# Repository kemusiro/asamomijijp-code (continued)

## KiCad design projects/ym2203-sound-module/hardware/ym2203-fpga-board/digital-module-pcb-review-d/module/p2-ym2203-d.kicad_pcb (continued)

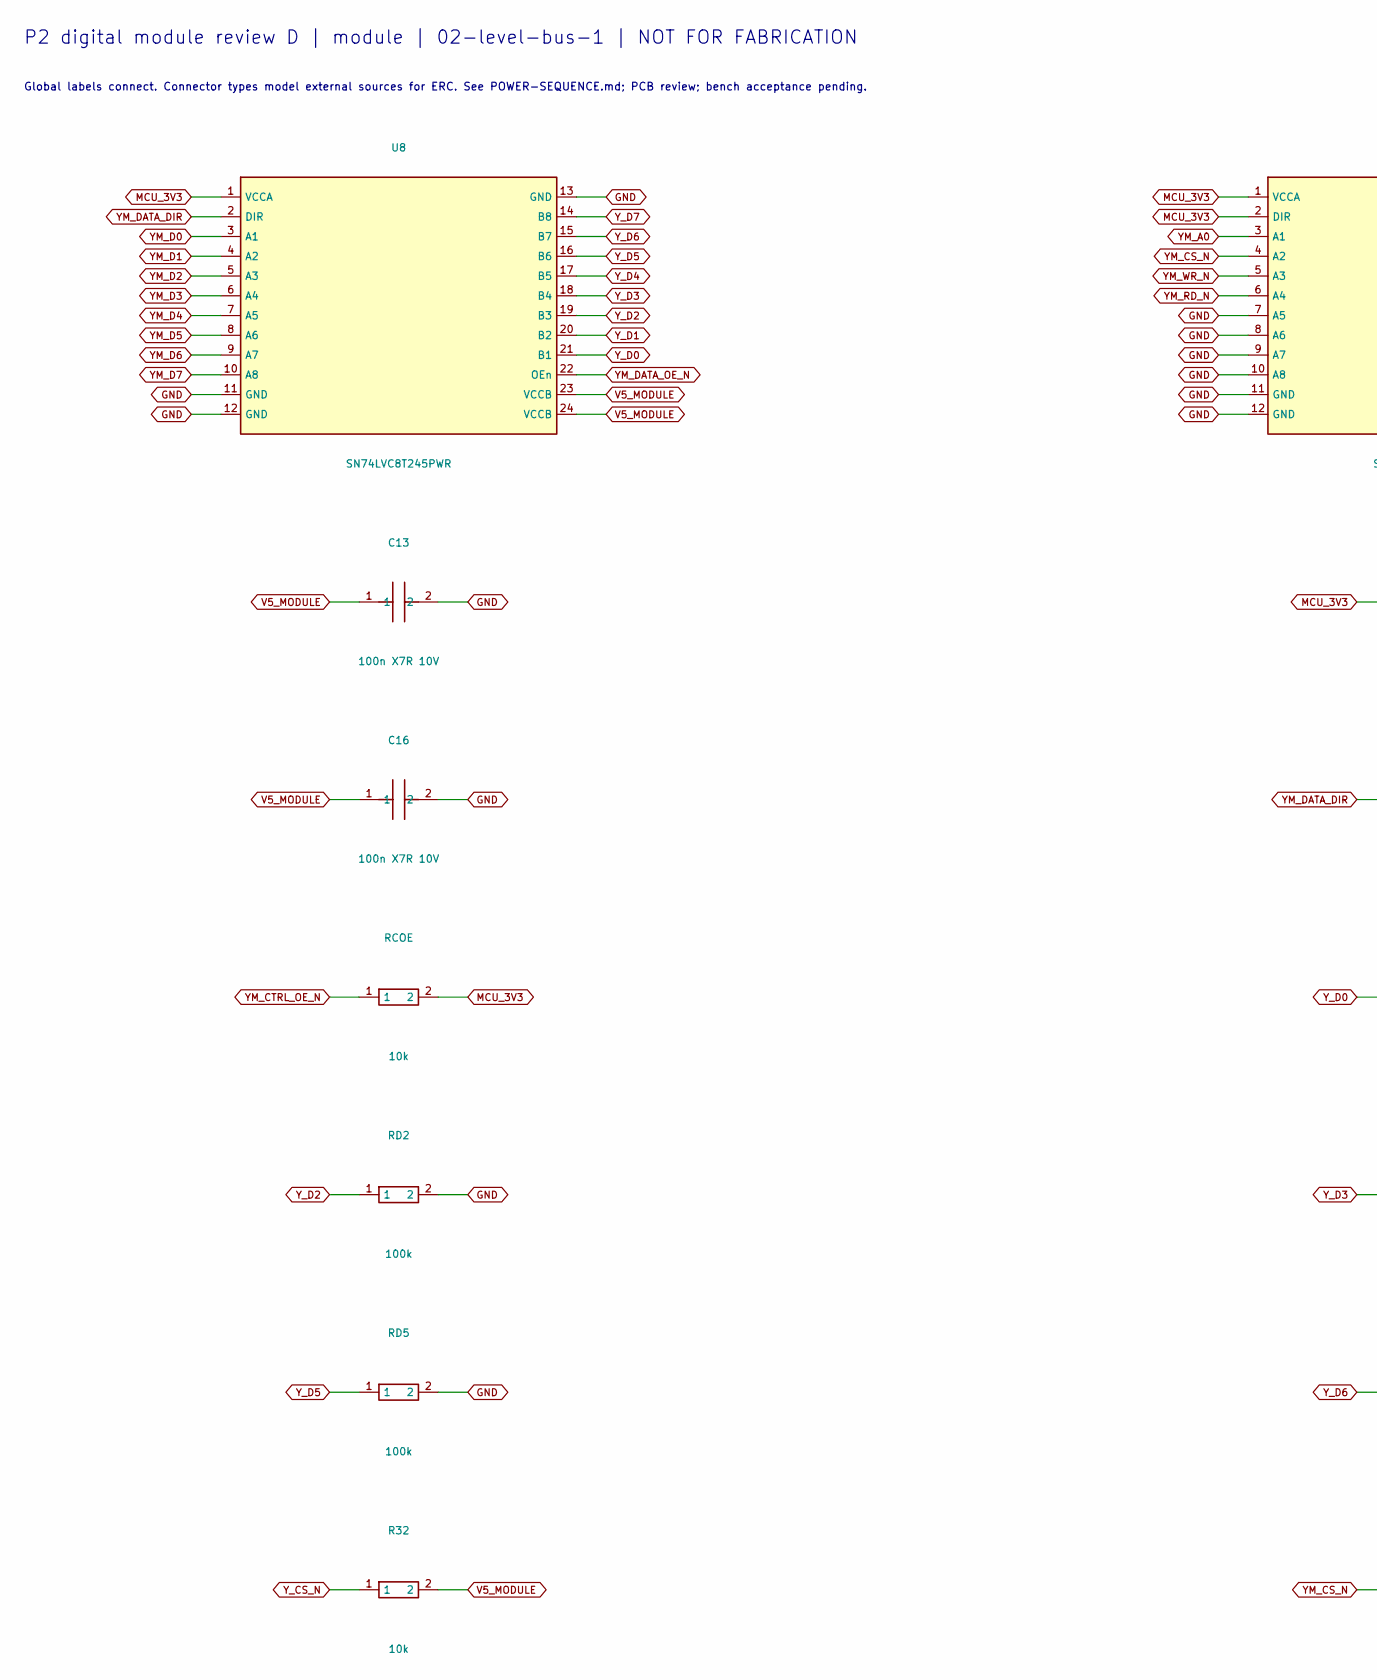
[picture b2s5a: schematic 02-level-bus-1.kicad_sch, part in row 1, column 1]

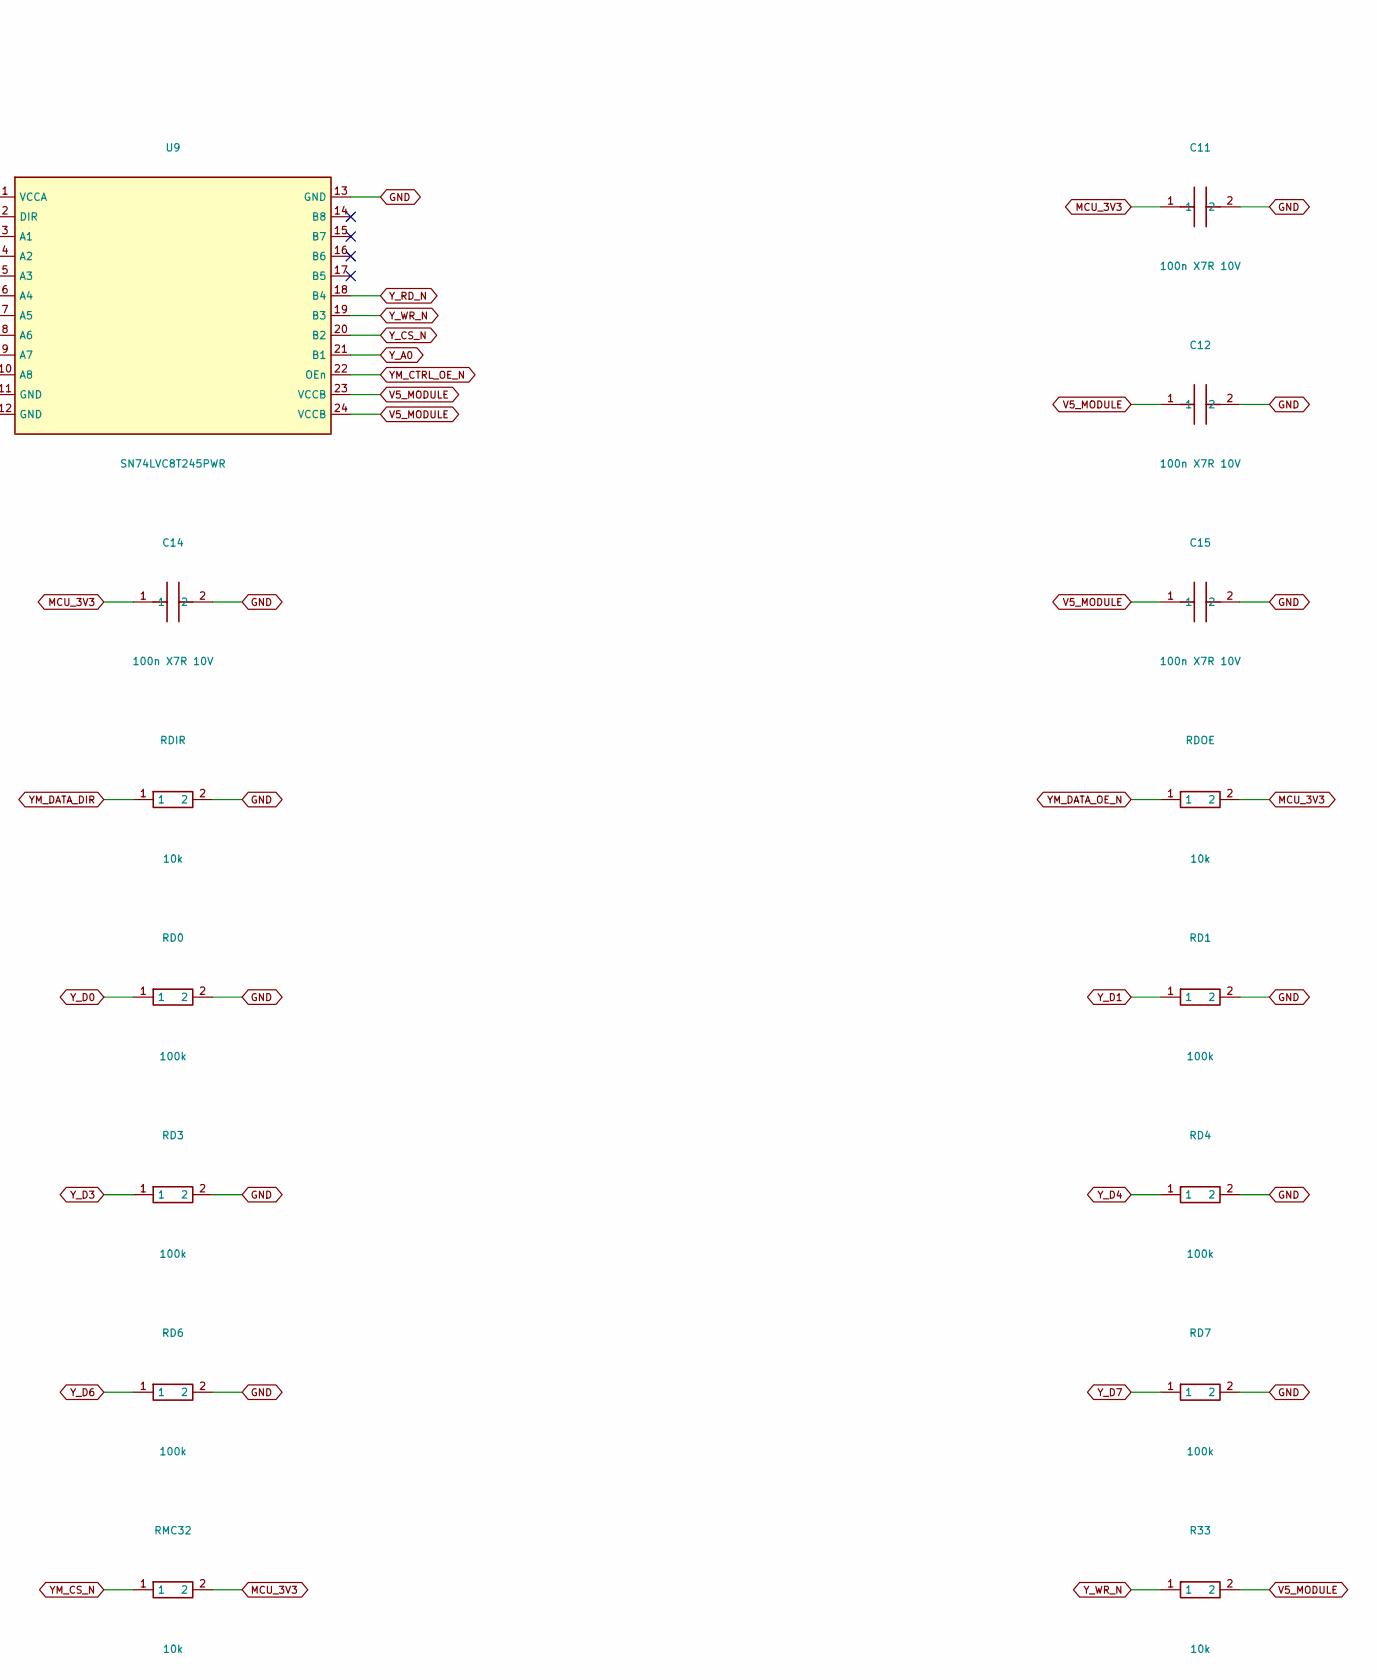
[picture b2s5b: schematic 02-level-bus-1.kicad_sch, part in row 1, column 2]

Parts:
C11, C12, C13, C14, C15, C16: 100n X7R 10V; C_0805_2012Metric
R32, R33: 10k; R_0805_2012Metric
RCOE: 10k; R_0805_2012Metric
RD0, RD1, RD2, RD3, RD4, RD5, RD6, RD7: 100k; R_0805_2012Metric
RDIR: 10k; R_0805_2012Metric
RDOE: 10k; R_0805_2012Metric
RMC32: 10k; R_0805_2012Metric
U8, U9: SN74LVC8T245PWR; TSSOP-24_4.4x7.8mm_P0.65mm

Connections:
GND: C11.2, C12.2, C13.2, C14.2, C15.2, C16.2, RD0.2, RD1.2, RD2.2, RD3.2, RD4.2, RD5.2, RD6.2, RD7.2, RDIR.2, U8.11 (GND), U8.12 (GND), U8.13 (GND), U9.7 (A5), U9.8 (A6), U9.9 (A7), U9.10 (A8), U9.11 (GND), U9.12 (GND), U9.13 (GND); also elsewhere on the board
MCU_3V3: C11.1, C14.1, RCOE.2, RDOE.2, RMC32.2, U8.1 (VCCA), U9.1 (VCCA), U9.2 (DIR); also elsewhere on the board
V5_MODULE: C12.1, C13.1, C15.1, C16.1, R32.2, R33.2, U8.23 (VCCB), U8.24 (VCCB), U9.23 (VCCB), U9.24 (VCCB); also elsewhere on the board
YM_A0: U9.3 (A1); also elsewhere on the board
YM_CS_N: RMC32.1, U9.4 (A2); also elsewhere on the board
YM_CTRL_OE_N: RCOE.1, U9.22 (OEn); also elsewhere on the board
YM_D0: U8.3 (A1); also elsewhere on the board
YM_D1: U8.4 (A2); also elsewhere on the board
YM_D2: U8.5 (A3); also elsewhere on the board
YM_D3: U8.6 (A4); also elsewhere on the board
YM_D4: U8.7 (A5); also elsewhere on the board
YM_D5: U8.8 (A6); also elsewhere on the board
YM_D6: U8.9 (A7); also elsewhere on the board
YM_D7: U8.10 (A8); also elsewhere on the board
YM_DATA_DIR: RDIR.1, U8.2 (DIR); also elsewhere on the board
YM_DATA_OE_N: RDOE.1, U8.22 (OEn); also elsewhere on the board
YM_RD_N: U9.6 (A4); also elsewhere on the board
YM_WR_N: U9.5 (A3); also elsewhere on the board
Y_A0: U9.21 (B1); also elsewhere on the board
Y_CS_N: R32.1, U9.20 (B2); also elsewhere on the board
Y_D0: RD0.1, U8.21 (B1); also elsewhere on the board
Y_D1: RD1.1, U8.20 (B2); also elsewhere on the board
Y_D2: RD2.1, U8.19 (B3); also elsewhere on the board
Y_D3: RD3.1, U8.18 (B4); also elsewhere on the board
Y_D4: RD4.1, U8.17 (B5); also elsewhere on the board
Y_D5: RD5.1, U8.16 (B6); also elsewhere on the board
Y_D6: RD6.1, U8.15 (B7); also elsewhere on the board
Y_D7: RD7.1, U8.14 (B8); also elsewhere on the board
Y_RD_N: U9.18 (B4); also elsewhere on the board
Y_WR_N: R33.1, U9.19 (B3); also elsewhere on the board

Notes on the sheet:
P2 digital module review D | module | 02-level-bus-1 | NOT FOR FABRICATION
Global labels connect. Connector types model external sources for ERC. See POWER-SEQUENCE.md; PCB review; bench acceptance pending.

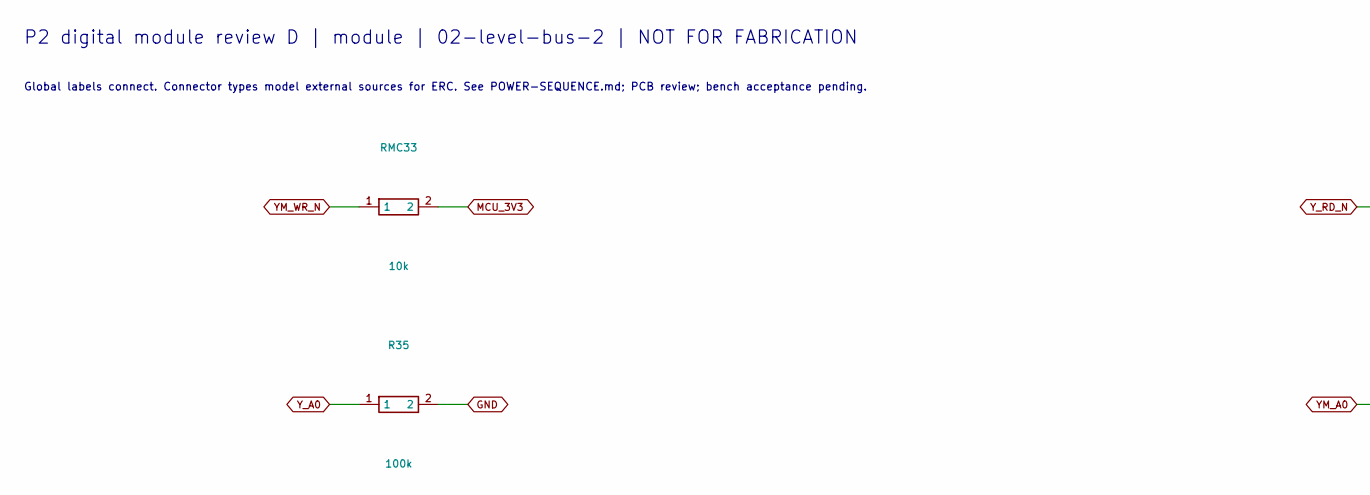
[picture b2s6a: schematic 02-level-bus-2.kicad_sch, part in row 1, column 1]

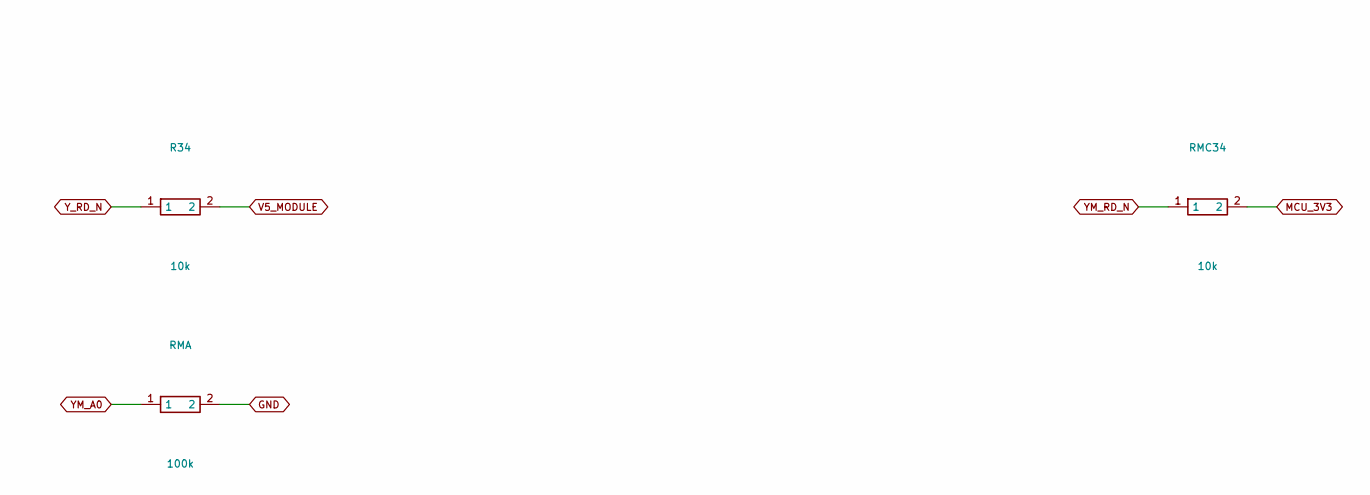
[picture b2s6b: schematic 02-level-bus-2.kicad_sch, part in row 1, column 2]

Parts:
R34: 10k; R_0805_2012Metric
R35: 100k; R_0805_2012Metric
RMA: 100k; R_0805_2012Metric
RMC33, RMC34: 10k; R_0805_2012Metric

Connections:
GND: R35.2, RMA.2; also elsewhere on the board
MCU_3V3: RMC33.2, RMC34.2; also elsewhere on the board
V5_MODULE: R34.2; also elsewhere on the board
YM_A0: RMA.1; also elsewhere on the board
YM_RD_N: RMC34.1; also elsewhere on the board
YM_WR_N: RMC33.1; also elsewhere on the board
Y_A0: R35.1; also elsewhere on the board
Y_RD_N: R34.1; also elsewhere on the board

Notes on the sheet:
P2 digital module review D | module | 02-level-bus-2 | NOT FOR FABRICATION
Global labels connect. Connector types model external sources for ERC. See POWER-SEQUENCE.md; PCB review; bench acceptance pending.

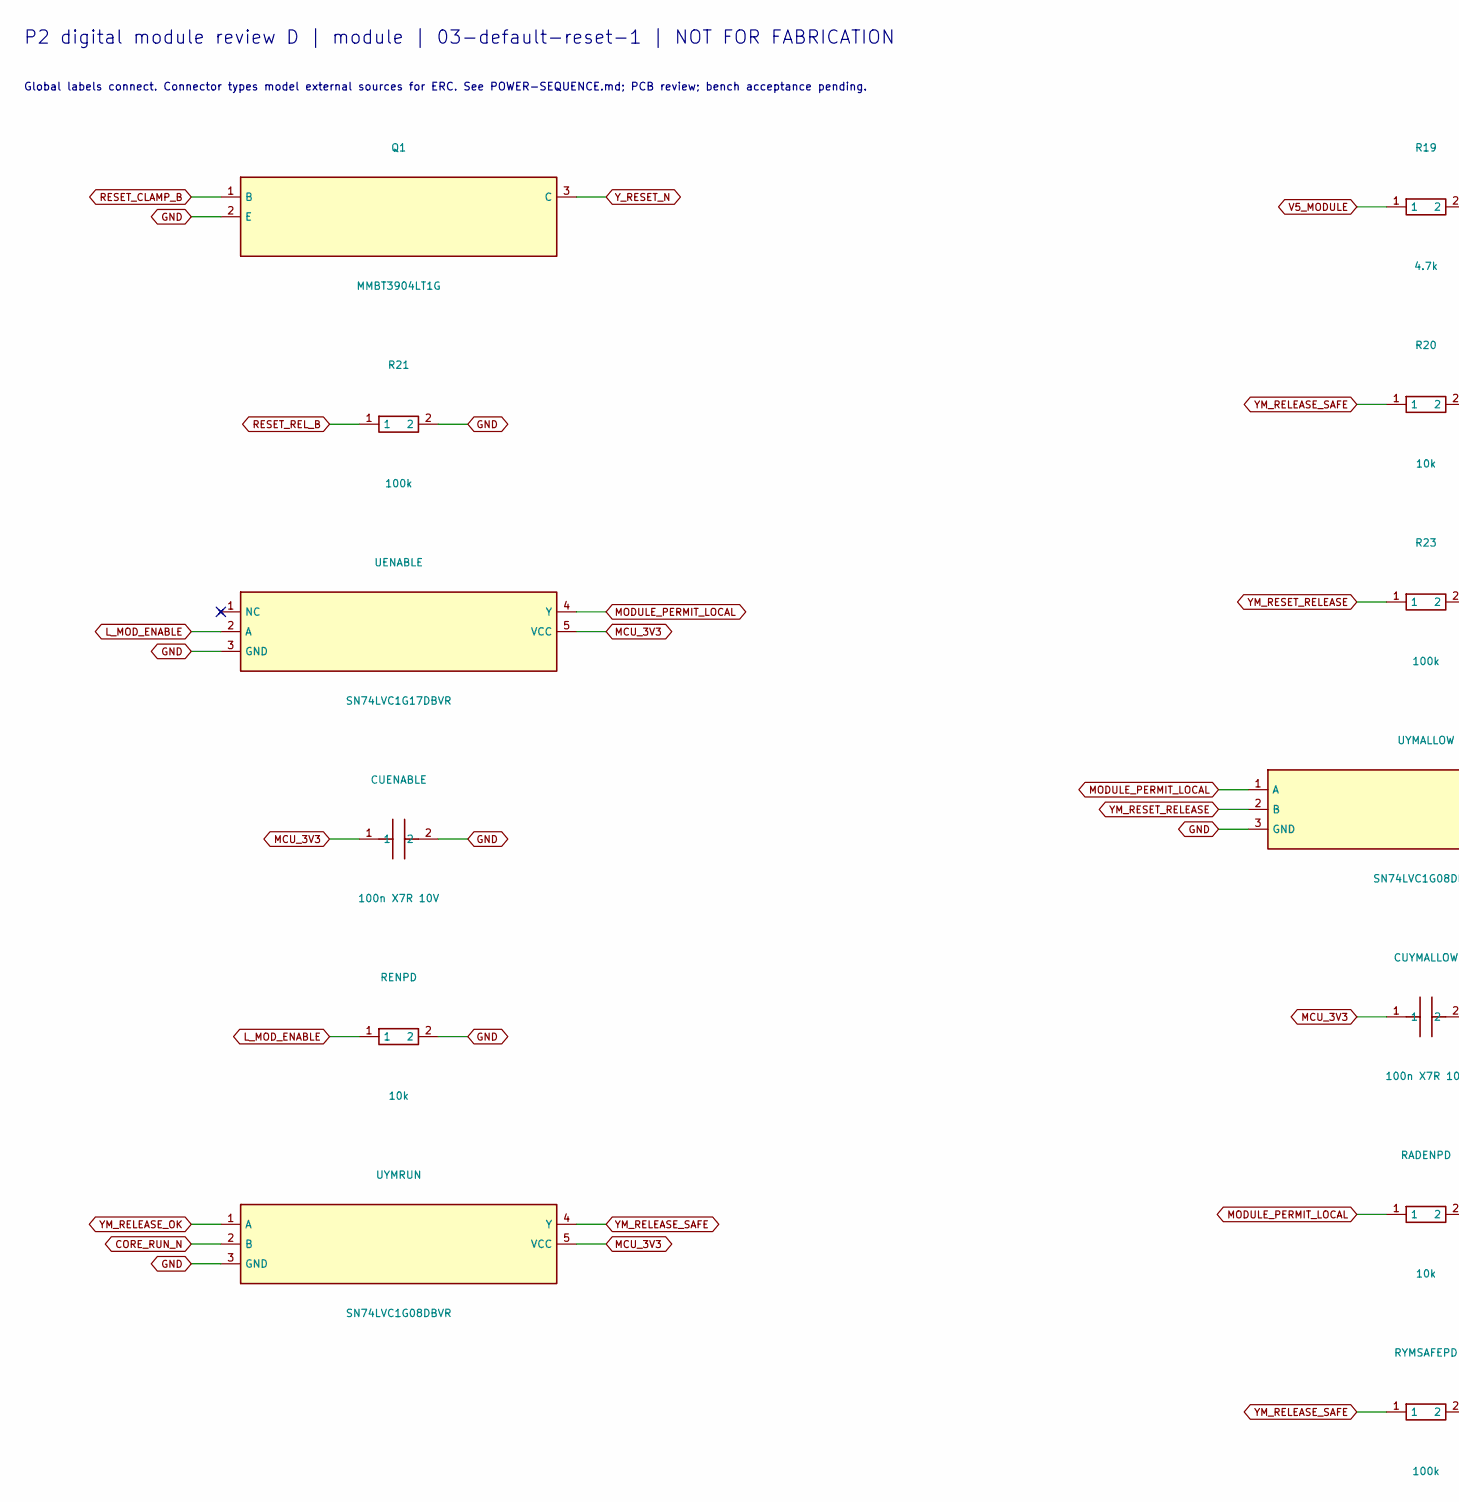
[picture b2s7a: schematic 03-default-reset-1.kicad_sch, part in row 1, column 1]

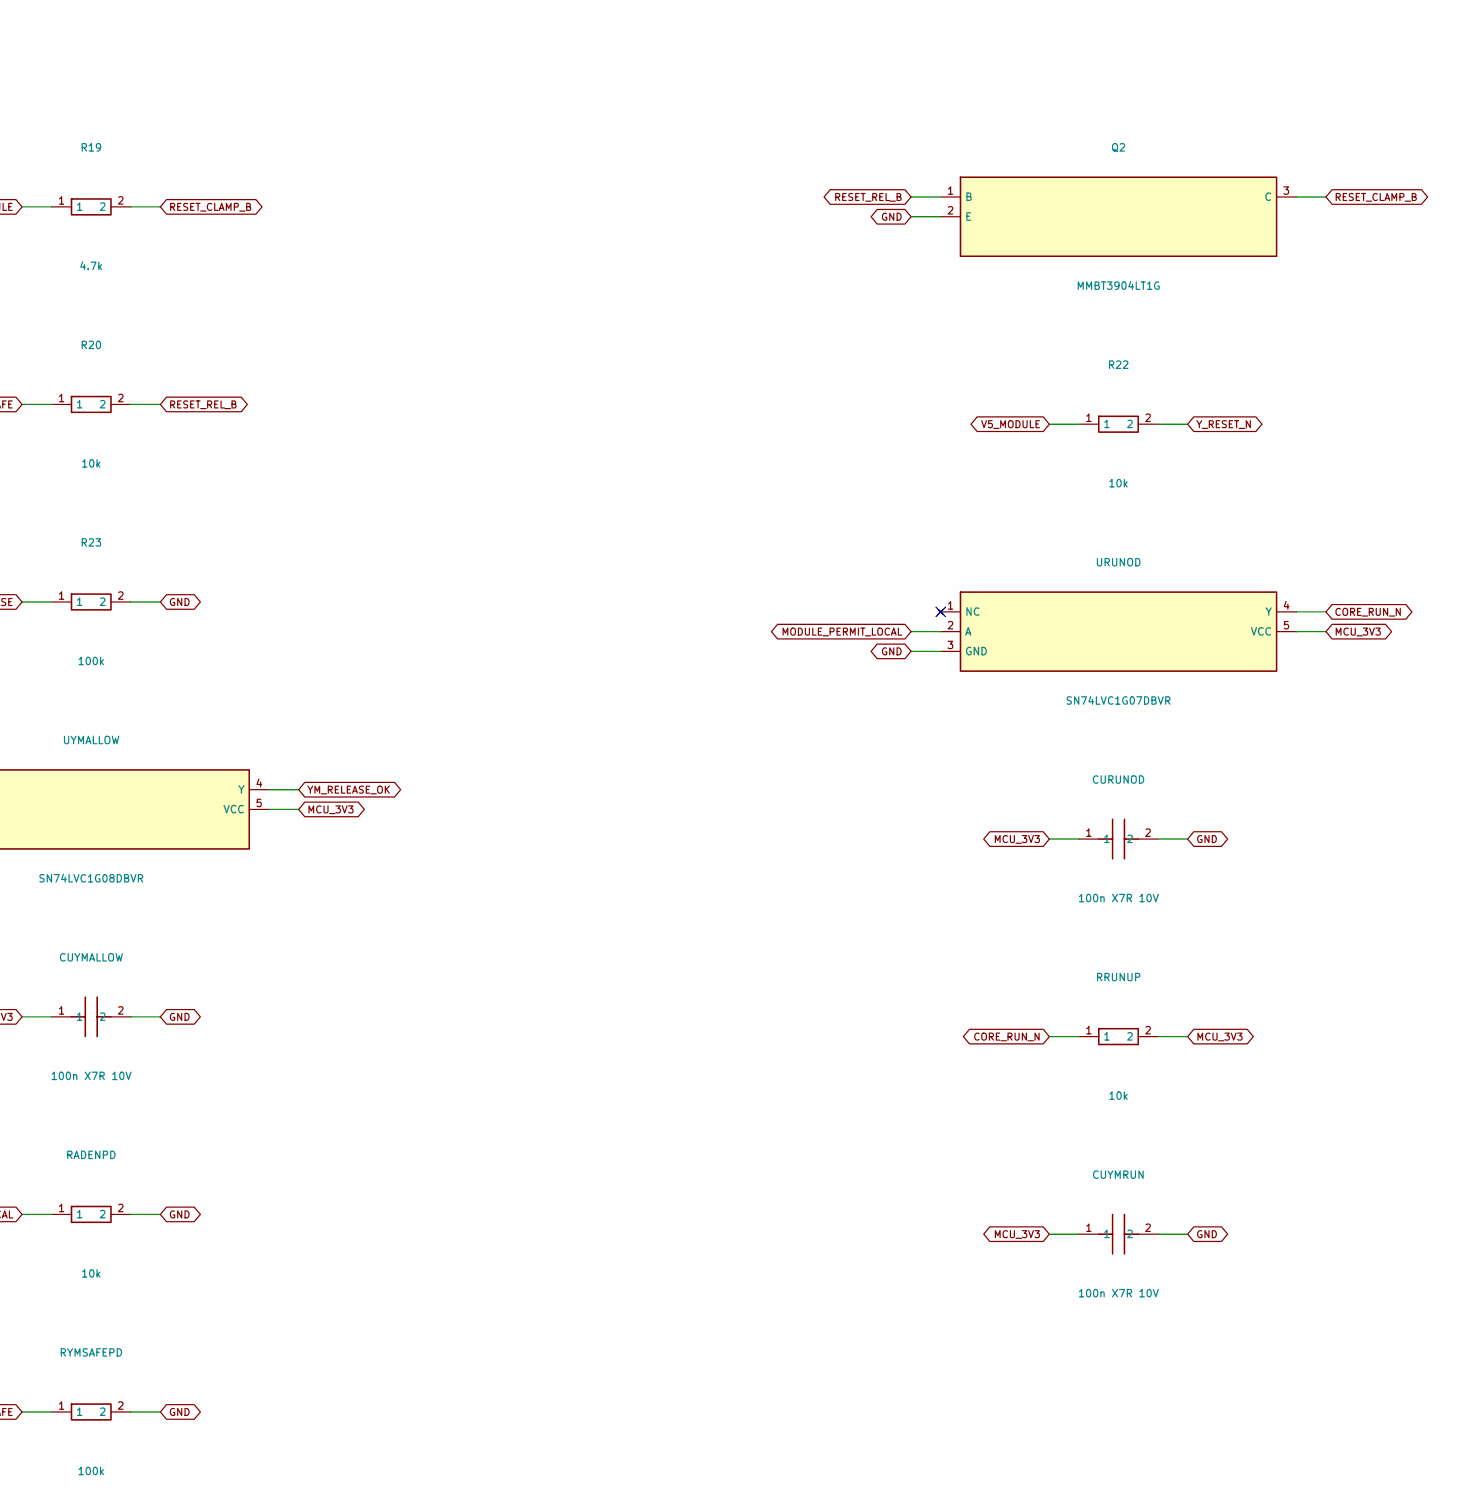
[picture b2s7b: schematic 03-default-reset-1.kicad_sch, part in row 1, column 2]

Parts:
CUENABLE: 100n X7R 10V; C_0805_2012Metric
CURUNOD: 100n X7R 10V; C_0805_2012Metric
CUYMALLOW: 100n X7R 10V; C_0805_2012Metric
CUYMRUN: 100n X7R 10V; C_0805_2012Metric
Q1, Q2: MMBT3904LT1G; SOT-23
R19: 4.7k; R_0805_2012Metric
R20, R22: 10k; R_0805_2012Metric
R21, R23: 100k; R_0805_2012Metric
RADENPD: 10k; R_0805_2012Metric
RENPD: 10k; R_0805_2012Metric
RRUNUP: 10k; R_0805_2012Metric
RYMSAFEPD: 100k; R_0805_2012Metric
UENABLE: SN74LVC1G17DBVR; SOT-23-5
URUNOD: SN74LVC1G07DBVR; SOT-23-5
UYMALLOW: SN74LVC1G08DBVR; SOT-23-5
UYMRUN: SN74LVC1G08DBVR; SOT-23-5

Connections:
CORE_RUN_N: RRUNUP.1, URUNOD.4 (Y), UYMRUN.2 (B); also elsewhere on the board
GND: CUENABLE.2, CURUNOD.2, CUYMALLOW.2, CUYMRUN.2, Q1.2 (E), Q2.2 (E), R21.2, R23.2, RADENPD.2, RENPD.2, RYMSAFEPD.2, UENABLE.3 (GND), URUNOD.3 (GND), UYMALLOW.3 (GND), UYMRUN.3 (GND); also elsewhere on the board
L_MOD_ENABLE: RENPD.1, UENABLE.2 (A); also elsewhere on the board
MCU_3V3: CUENABLE.1, CURUNOD.1, CUYMALLOW.1, CUYMRUN.1, RRUNUP.2, UENABLE.5 (VCC), URUNOD.5 (VCC), UYMALLOW.5 (VCC), UYMRUN.5 (VCC); also elsewhere on the board
MODULE_PERMIT_LOCAL: RADENPD.1, UENABLE.4 (Y), URUNOD.2 (A), UYMALLOW.1 (A); also elsewhere on the board
RESET_CLAMP_B: Q1.1 (B), Q2.3 (C), R19.2
RESET_REL_B: Q2.1 (B), R20.2, R21.1
V5_MODULE: R19.1, R22.1; also elsewhere on the board
YM_RELEASE_OK: UYMALLOW.4 (Y), UYMRUN.1 (A)
YM_RELEASE_SAFE: R20.1, RYMSAFEPD.1, UYMRUN.4 (Y); also elsewhere on the board
YM_RESET_RELEASE: R23.1, UYMALLOW.2 (B); also elsewhere on the board
Y_RESET_N: Q1.3 (C), R22.2; also elsewhere on the board

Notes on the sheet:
P2 digital module review D | module | 03-default-reset-1 | NOT FOR FABRICATION
Global labels connect. Connector types model external sources for ERC. See POWER-SEQUENCE.md; PCB review; bench acceptance pending.

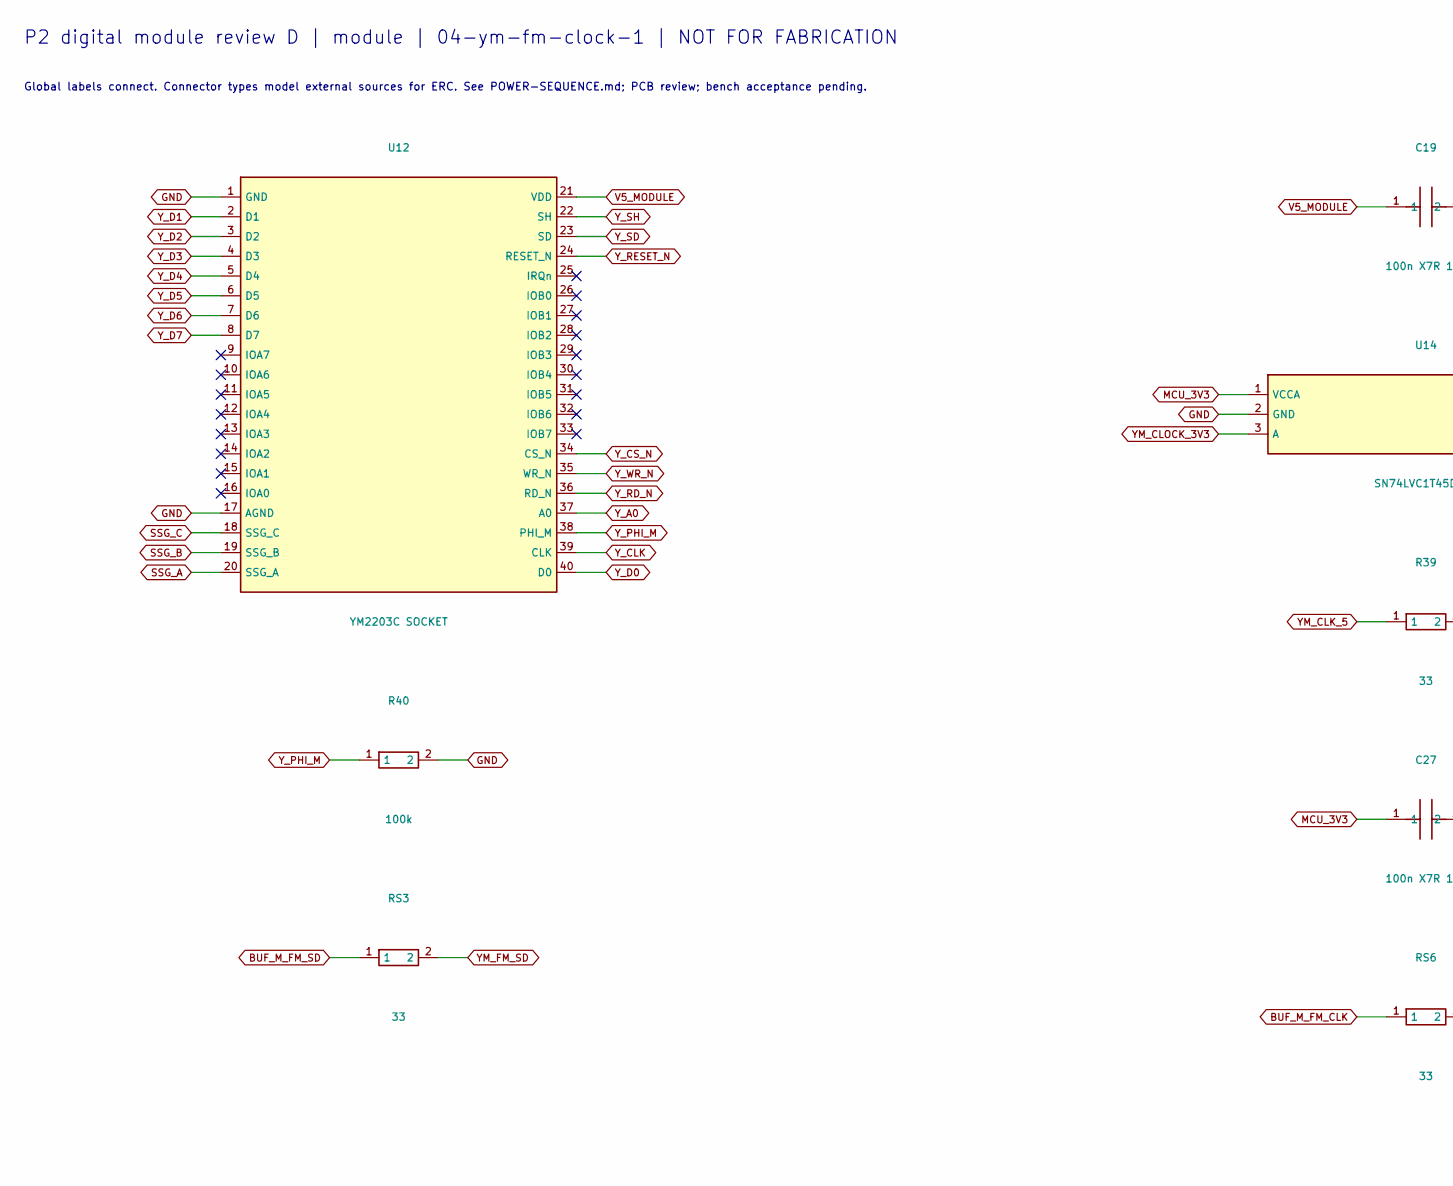
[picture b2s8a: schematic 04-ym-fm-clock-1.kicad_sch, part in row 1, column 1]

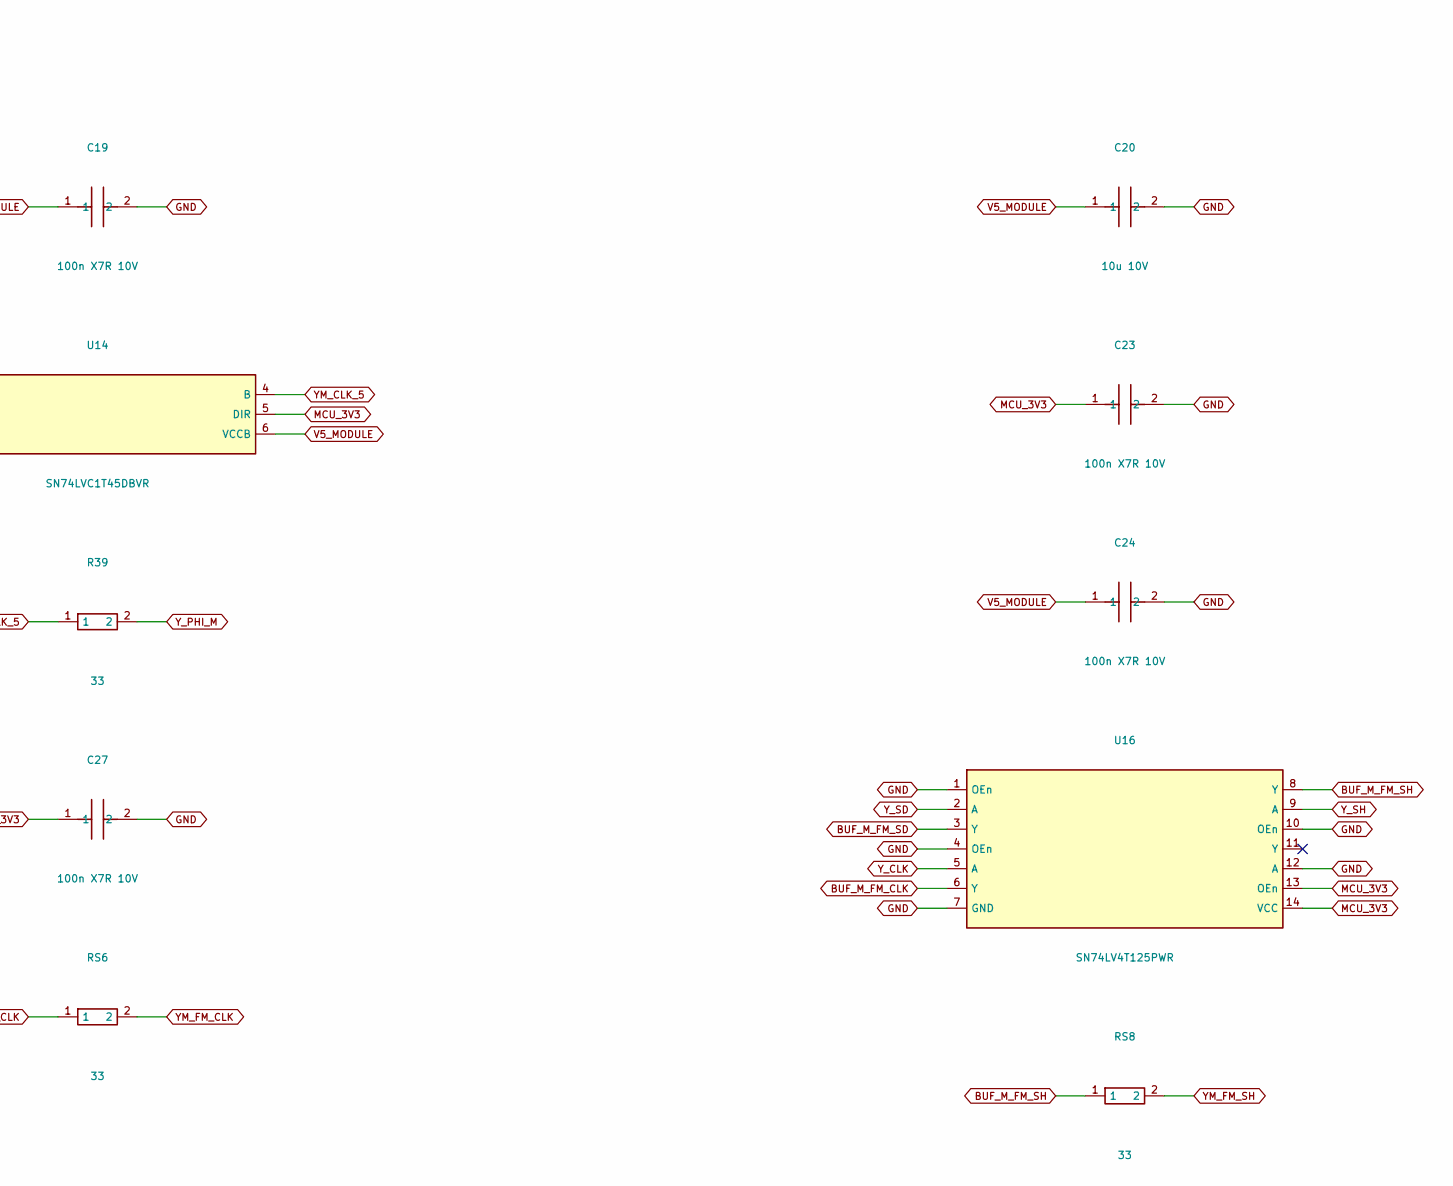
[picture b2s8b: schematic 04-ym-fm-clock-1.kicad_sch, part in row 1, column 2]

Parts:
C19, C23, C24, C27: 100n X7R 10V; C_0805_2012Metric
C20: 10u 10V; C_0805_2012Metric
R39: 33; R_0805_2012Metric
R40: 100k; R_0805_2012Metric
RS3, RS6, RS8: 33; R_0805_2012Metric
U12: YM2203C SOCKET; DIP-40_W15.24mm_Socket
U14: SN74LVC1T45DBVR; SOT-23-6
U16: SN74LV4T125PWR; TSSOP-14_4.4x5mm_P0.65mm

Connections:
BUF_M_FM_CLK: RS6.1, U16.6 (Y)
BUF_M_FM_SD: RS3.1, U16.3 (Y)
BUF_M_FM_SH: RS8.1, U16.8 (Y)
GND: C19.2, C20.2, C23.2, C24.2, C27.2, R40.2, U12.1 (GND), U12.17 (AGND), U14.2 (GND), U16.1 (OEn), U16.4 (OEn), U16.7 (GND), U16.10 (OEn), U16.12 (A); also elsewhere on the board
MCU_3V3: C23.1, C27.1, U14.1 (VCCA), U14.5 (DIR), U16.13 (OEn), U16.14 (VCC); also elsewhere on the board
SSG_A: U12.20 (SSG_A); also elsewhere on the board
SSG_B: U12.19 (SSG_B); also elsewhere on the board
SSG_C: U12.18 (SSG_C); also elsewhere on the board
V5_MODULE: C19.1, C20.1, C24.1, U12.21 (VDD), U14.6 (VCCB); also elsewhere on the board
YM_CLK_5: R39.1, U14.4 (B)
YM_CLOCK_3V3: U14.3 (A); also elsewhere on the board
YM_FM_CLK: RS6.2; also elsewhere on the board
YM_FM_SD: RS3.2; also elsewhere on the board
YM_FM_SH: RS8.2; also elsewhere on the board
Y_A0: U12.37 (A0); also elsewhere on the board
Y_CLK: U12.39 (CLK), U16.5 (A)
Y_CS_N: U12.34 (CS_N); also elsewhere on the board
Y_D0: U12.40 (D0); also elsewhere on the board
Y_D1: U12.2 (D1); also elsewhere on the board
Y_D2: U12.3 (D2); also elsewhere on the board
Y_D3: U12.4 (D3); also elsewhere on the board
Y_D4: U12.5 (D4); also elsewhere on the board
Y_D5: U12.6 (D5); also elsewhere on the board
Y_D6: U12.7 (D6); also elsewhere on the board
Y_D7: U12.8 (D7); also elsewhere on the board
Y_PHI_M: R39.2, R40.1, U12.38 (PHI_M)
Y_RD_N: U12.36 (RD_N); also elsewhere on the board
Y_RESET_N: U12.24 (RESET_N); also elsewhere on the board
Y_SD: U12.23 (SD), U16.2 (A)
Y_SH: U12.22 (SH), U16.9 (A)
Y_WR_N: U12.35 (WR_N); also elsewhere on the board

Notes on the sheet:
P2 digital module review D | module | 04-ym-fm-clock-1 | NOT FOR FABRICATION
Global labels connect. Connector types model external sources for ERC. See POWER-SEQUENCE.md; PCB review; bench acceptance pending.

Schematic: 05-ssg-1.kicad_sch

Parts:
RL0, RL1, RL2: 1.33k 1%; R_0805_2012Metric

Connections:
GND: RL0.2, RL1.2, RL2.2; also elsewhere on the board
SSG_A: RL0.1; also elsewhere on the board
SSG_B: RL1.1; also elsewhere on the board
SSG_C: RL2.1; also elsewhere on the board

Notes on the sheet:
P2 digital module review D | module | 05-ssg-1 | NOT FOR FABRICATION
Global labels connect. Connector types model external sources for ERC. See POWER-SEQUENCE.md; PCB review; bench acceptance pending.

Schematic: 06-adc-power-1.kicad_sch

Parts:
CADCIN: 4.7u X7R 10V; C_0805_2012Metric
CADCOUT: 4.7u X7R 10V; C_0805_2012Metric
CMOD5: 22u X7R 10V; C_0805_2012Metric
RADCBLEED: 680; R_0805_2012Metric
UADCPOWER: TLV75533PDBVR; SOT-23-5

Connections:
ADC_3V3: CADCOUT.1, RADCBLEED.1, UADCPOWER.5 (OUT); also elsewhere on the board
GND: CADCIN.2, CADCOUT.2, CMOD5.2, RADCBLEED.2, UADCPOWER.2 (GND); also elsewhere on the board
MODULE_PERMIT_LOCAL: UADCPOWER.3 (EN); also elsewhere on the board
V5_MODULE: CADCIN.1, CMOD5.1, UADCPOWER.1 (IN); also elsewhere on the board

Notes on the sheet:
P2 digital module review D | module | 06-adc-power-1 | NOT FOR FABRICATION
Global labels connect. Connector types model external sources for ERC. See POWER-SEQUENCE.md; PCB review; bench acceptance pending.

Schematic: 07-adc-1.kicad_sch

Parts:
CADCAV0: 100n X7R 10V; C_0805_2012Metric
CADCAV1: 10u X7R 10V; C_0805_2012Metric
CADCDV0: 100n X7R 10V; C_0805_2012Metric
CADCDV1: 10u X7R 10V; C_0805_2012Metric
CADCIO0: 100n X7R 10V; C_0805_2012Metric
CADCIO1: 10u X7R 10V; C_0805_2012Metric
CADCLDO0: 100n X7R 10V; C_0805_2012Metric
CADCLDO1: 10u X7R 10V; C_0805_2012Metric
CADCVREF: 1u X7R 10V; C_0805_2012Metric
CUADCCLK: 100n X7R 10V; C_0805_2012Metric
CUADCDATA: 100n X7R 10V; C_0805_2012Metric
RADCDATAPD: 100k; R_0805_2012Metric
RADCSCL: 4.7k; R_0805_2012Metric
RADCSDA: 4.7k; R_0805_2012Metric
RDMINPD: 100k; R_0805_2012Metric
UADC: PCM1863DBT; TSSOP-30_4.4x7.8mm_P0.5mm
UADCCLK: SN74LV4T125PWR; TSSOP-14_4.4x5mm_P0.65mm
UADCDATA: SN74LVC1G125DBVR; SOT-23-5

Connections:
ADC_3V3: CADCAV0.1, CADCAV1.1, CADCDV0.1, CADCDV1.1, CADCIO0.1, CADCIO1.1, CUADCCLK.1, RADCSCL.2, RADCSDA.2, UADC.8 (AVDD), UADC.13 (DVDD), UADC.14 (IOVDD), UADCCLK.10 (3OE_N), UADCCLK.13 (4OE_N), UADCCLK.14 (VCC); also elsewhere on the board
ADC_BCK: UADC.17 (BCK), UADCCLK.3 (1Y)
ADC_DMIN_PD: RDMINPD.1, UADC.21 (GPIO1_DMIN)
ADC_DOUT: RADCDATAPD.1, UADCDATA.4 (Y); also elsewhere on the board
ADC_DOUT_RAW: UADC.18 (DOUT), UADCDATA.2 (A)
ADC_INPUT_ARM: UADC.19 (GPIO3_INPUT_ARM); also elsewhere on the board
ADC_LDO_1V8: CADCLDO0.1, CADCLDO1.1, UADC.11 (LDO_1V8)
ADC_LRCK: UADC.16 (LRCK), UADCCLK.6 (2Y)
ADC_SCL: RADCSCL.1, UADC.24 (SCL); also elsewhere on the board
ADC_SDA: RADCSDA.1, UADC.23 (SDA); also elsewhere on the board
ADC_SSG_A: UADC.3 (VINL1); also elsewhere on the board
ADC_SSG_B: UADC.1 (VINL2); also elsewhere on the board
ADC_SSG_C: UADC.29 (VINL3); also elsewhere on the board
ADC_VREF: CADCVREF.1, UADC.6 (VREF)
GND: CADCAV0.2, CADCAV1.2, CADCDV0.2, CADCDV1.2, CADCIO0.2, CADCIO1.2, CADCLDO0.2, CADCLDO1.2, CADCVREF.2, CUADCCLK.2, CUADCDATA.2, RADCDATAPD.2, RDMINPD.2, UADC.7 (AGND), UADC.10 (XI), UADC.12 (DGND), UADC.15 (SCKI), UADC.25 (AD), UADC.26 (MD0_I2C), UADCCLK.1 (1OE_N), UADCCLK.4 (2OE_N), UADCCLK.7 (GND), UADCCLK.9 (3A), UADCCLK.12 (4A), UADCDATA.1 (OE_N), UADCDATA.3 (GND); also elsewhere on the board
MCU_3V3: CUADCDATA.1, UADCDATA.5 (VCC); also elsewhere on the board
MOD_I2S_BCK: UADCCLK.2 (1A); also elsewhere on the board
MOD_I2S_LRCK: UADCCLK.5 (2A); also elsewhere on the board

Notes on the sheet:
P2 digital module review D | module | 07-adc-1 | NOT FOR FABRICATION
Global labels connect. Connector types model external sources for ERC. See POWER-SEQUENCE.md; PCB review; bench acceptance pending.

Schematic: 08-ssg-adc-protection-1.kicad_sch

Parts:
CAAFA: 470p C0G; C_0805_2012Metric
CAAFB: 470p C0G; C_0805_2012Metric
CACA: 2.2u X7R 10V; C_0805_2012Metric
CACB: 2.2u X7R 10V; C_0805_2012Metric
CACC: 2.2u X7R 10V; C_0805_2012Metric
CUINPUT: 100n X7R 10V; C_0805_2012Metric
CUINPUTAND: 100n X7R 10V; C_0805_2012Metric
DCLAMPA: BAT54S,215; SOT-23
DCLAMPB: BAT54S,215; SOT-23
RADCARM: 10k; R_0805_2012Metric
RADCLIMITA: 4.7k 1%; R_0805_2012Metric
RADCLIMITB: 4.7k 1%; R_0805_2012Metric
RDIVBA: 1k 1%; R_0805_2012Metric
RDIVBB: 1k 1%; R_0805_2012Metric
RDIVBC: 1k 1%; R_0805_2012Metric
RDIVTA: 3.01k 1%; R_0805_2012Metric
RDIVTB: 3.01k 1%; R_0805_2012Metric
RDIVTC: 3.01k 1%; R_0805_2012Metric
RISOBLEEDA: 100k; R_0805_2012Metric
RISOBLEEDB: 100k; R_0805_2012Metric
RISOBLEEDC: 100k; R_0805_2012Metric
RMUXPD: 10k; R_0805_2012Metric
UINPUT: TMUX1511PWR; TSSOP-14_4.4x5mm_P0.65mm
UINPUTAND: SN74LVC1G08DBVR; SOT-23-5

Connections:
ADC_3V3: CUINPUT.1, CUINPUTAND.1, DCLAMPA.2 (K2), DCLAMPB.2 (K2), UINPUT.14 (VDD), UINPUTAND.5 (VCC); also elsewhere on the board
ADC_INPUT_ARM: RADCARM.1, UINPUTAND.1 (A); also elsewhere on the board
ADC_INPUT_ENABLE: RMUXPD.1, UINPUT.1 (SEL1), UINPUT.4 (SEL2), UINPUT.10 (SEL3), UINPUTAND.4 (Y); also elsewhere on the board
ADC_SSG_A: CAAFA.1, DCLAMPA.3 (K1_A2), RADCLIMITA.2; also elsewhere on the board
ADC_SSG_B: CAAFB.1, DCLAMPB.3 (K1_A2), RADCLIMITB.2; also elsewhere on the board
GND: CAAFA.2, CAAFB.2, CUINPUT.2, CUINPUTAND.2, DCLAMPA.1 (A1), DCLAMPB.1 (A1), RADCARM.2, RDIVBA.2, RDIVBB.2, RDIVBC.2, RISOBLEEDA.2, RISOBLEEDB.2, RISOBLEEDC.2, RMUXPD.2, UINPUT.7 (GND), UINPUT.12 (S4), UINPUT.13 (SEL4), UINPUTAND.3 (GND); also elsewhere on the board
SSG_A: RDIVTA.1; also elsewhere on the board
SSG_AC_A: CACA.2, RADCLIMITA.1
SSG_AC_B: CACB.2, RADCLIMITB.1
SSG_AC_C: CACC.2; also elsewhere on the board
SSG_B: RDIVTB.1; also elsewhere on the board
SSG_C: RDIVTC.1; also elsewhere on the board
SSG_DIV_A: RDIVBA.1, RDIVTA.2, UINPUT.2 (S1)
SSG_DIV_B: RDIVBB.1, RDIVTB.2, UINPUT.5 (S2)
SSG_DIV_C: RDIVBC.1, RDIVTC.2, UINPUT.9 (S3)
SSG_ISO_A: CACA.1, RISOBLEEDA.1, UINPUT.3 (D1)
SSG_ISO_B: CACB.1, RISOBLEEDB.1, UINPUT.6 (D2)
SSG_ISO_C: CACC.1, RISOBLEEDC.1, UINPUT.8 (D3)
YM_RELEASE_SAFE: UINPUTAND.2 (B); also elsewhere on the board

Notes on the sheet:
P2 digital module review D | module | 08-ssg-adc-protection-1 | NOT FOR FABRICATION
Global labels connect. Connector types model external sources for ERC. See POWER-SEQUENCE.md; PCB review; bench acceptance pending.

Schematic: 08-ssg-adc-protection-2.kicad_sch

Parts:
CAAFC: 470p C0G; C_0805_2012Metric
DCLAMPC: BAT54S,215; SOT-23
RADCLIMITC: 4.7k 1%; R_0805_2012Metric

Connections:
ADC_3V3: DCLAMPC.2 (K2); also elsewhere on the board
ADC_SSG_C: CAAFC.1, DCLAMPC.3 (K1_A2), RADCLIMITC.2; also elsewhere on the board
GND: CAAFC.2, DCLAMPC.1 (A1); also elsewhere on the board
SSG_AC_C: RADCLIMITC.1; also elsewhere on the board

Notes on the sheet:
P2 digital module review D | module | 08-ssg-adc-protection-2 | NOT FOR FABRICATION
Global labels connect. Connector types model external sources for ERC. See POWER-SEQUENCE.md; PCB review; bench acceptance pending.

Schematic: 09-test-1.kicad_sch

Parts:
TPADC3: ADC_3V3; TestPoint_Pad_D1.5mm
TPADCEN: MODULE_PERMIT_LOCAL; TestPoint_Pad_D1.5mm
TPARM: ADC_INPUT_ENABLE; TestPoint_Pad_D1.5mm
TPM3: MCU_3V3; TestPoint_Pad_D1.5mm
TPRESET: Y_RESET_N; TestPoint_Pad_D1.5mm

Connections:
ADC_3V3: TPADC3.1; also elsewhere on the board
ADC_INPUT_ENABLE: TPARM.1; also elsewhere on the board
MCU_3V3: TPM3.1; also elsewhere on the board
MODULE_PERMIT_LOCAL: TPADCEN.1; also elsewhere on the board
Y_RESET_N: TPRESET.1; also elsewhere on the board

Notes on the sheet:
P2 digital module review D | module | 09-test-1 | NOT FOR FABRICATION
Global labels connect. Connector types model external sources for ERC. See POWER-SEQUENCE.md; PCB review; bench acceptance pending.
